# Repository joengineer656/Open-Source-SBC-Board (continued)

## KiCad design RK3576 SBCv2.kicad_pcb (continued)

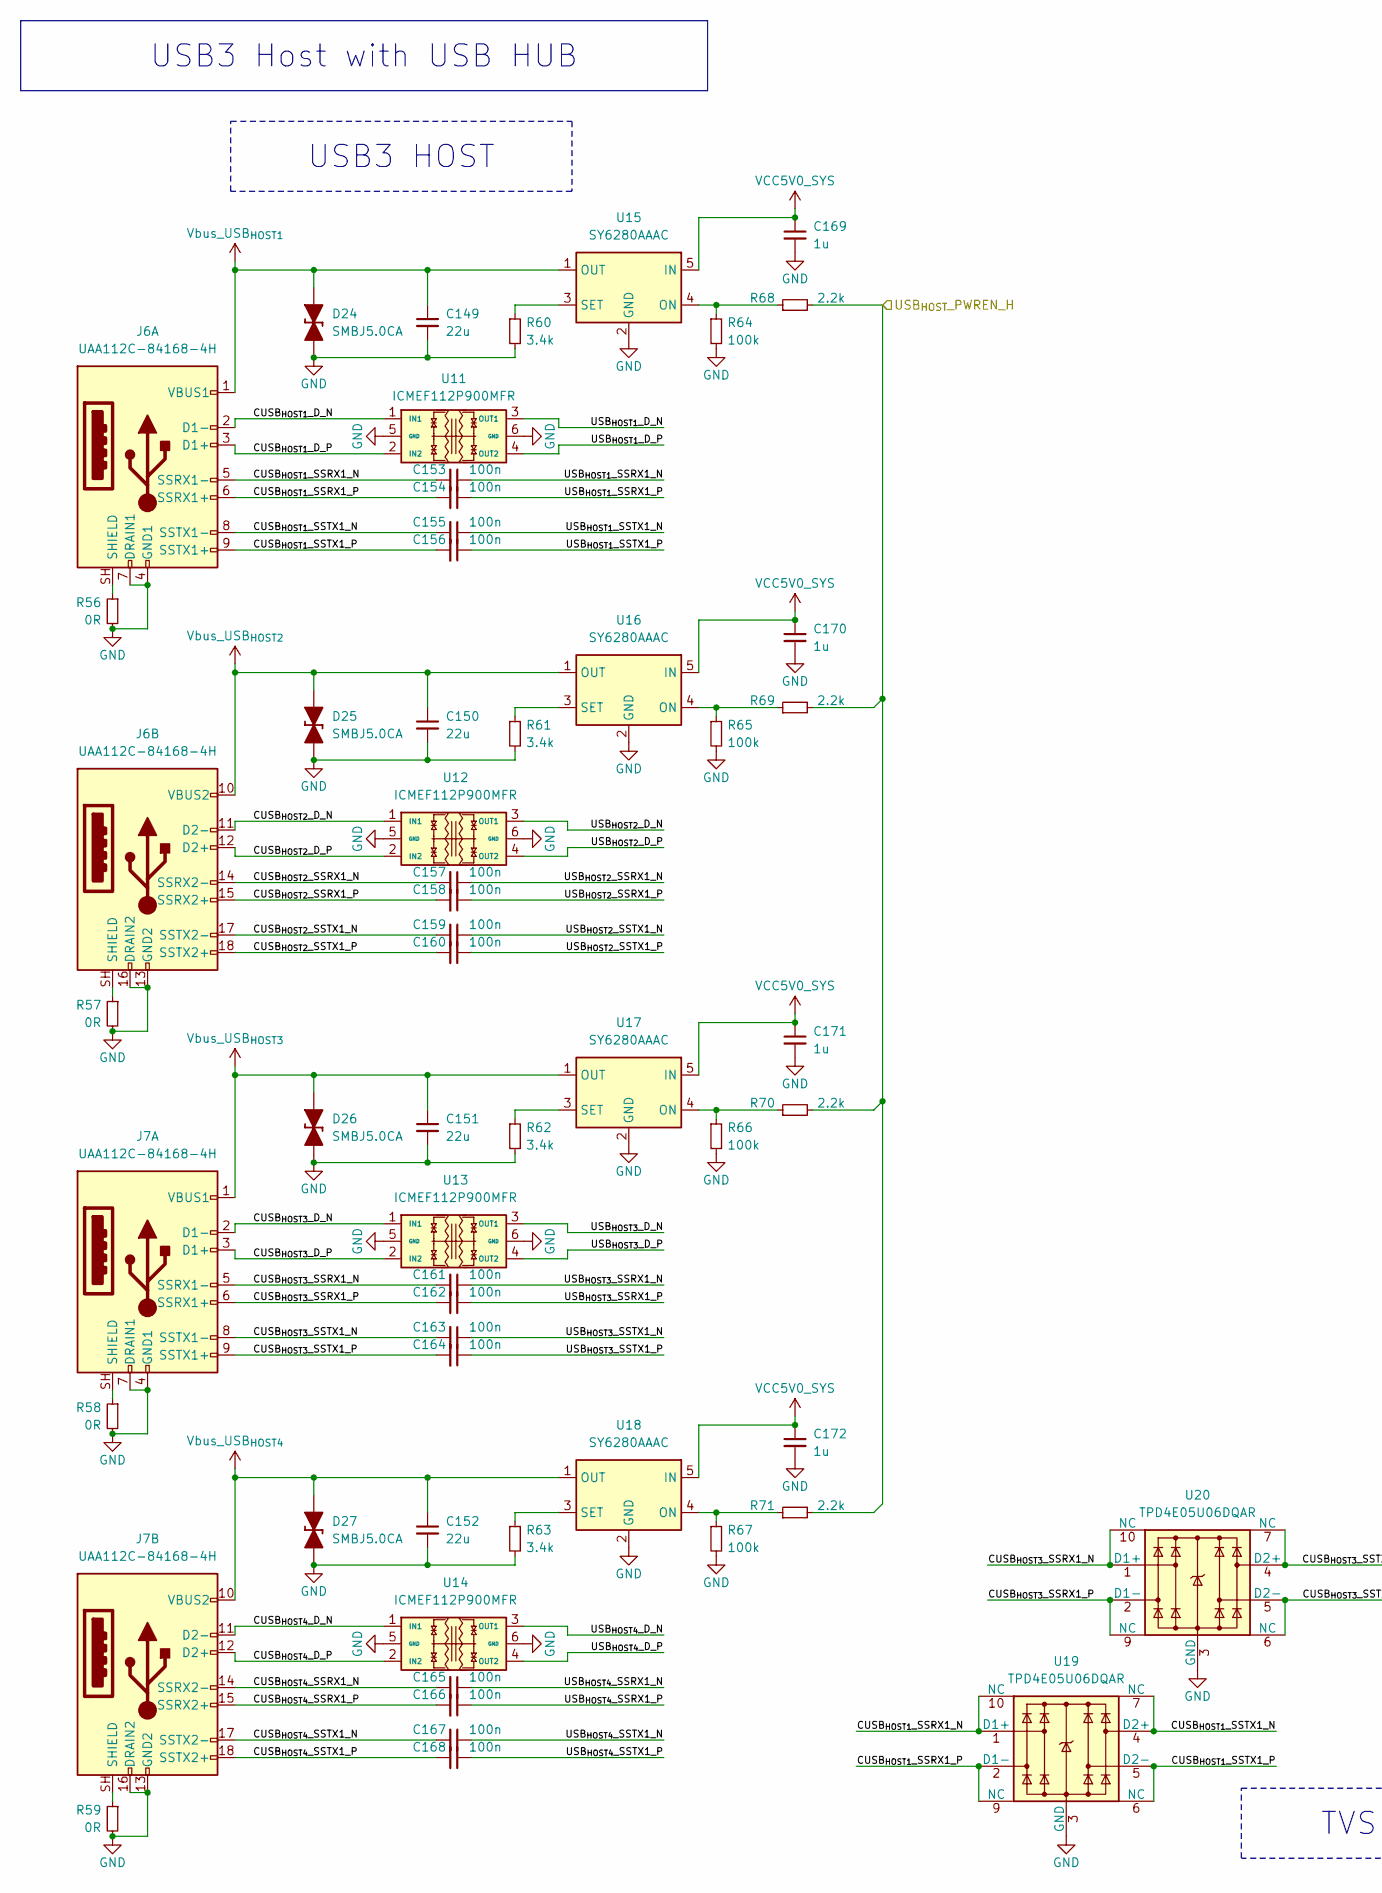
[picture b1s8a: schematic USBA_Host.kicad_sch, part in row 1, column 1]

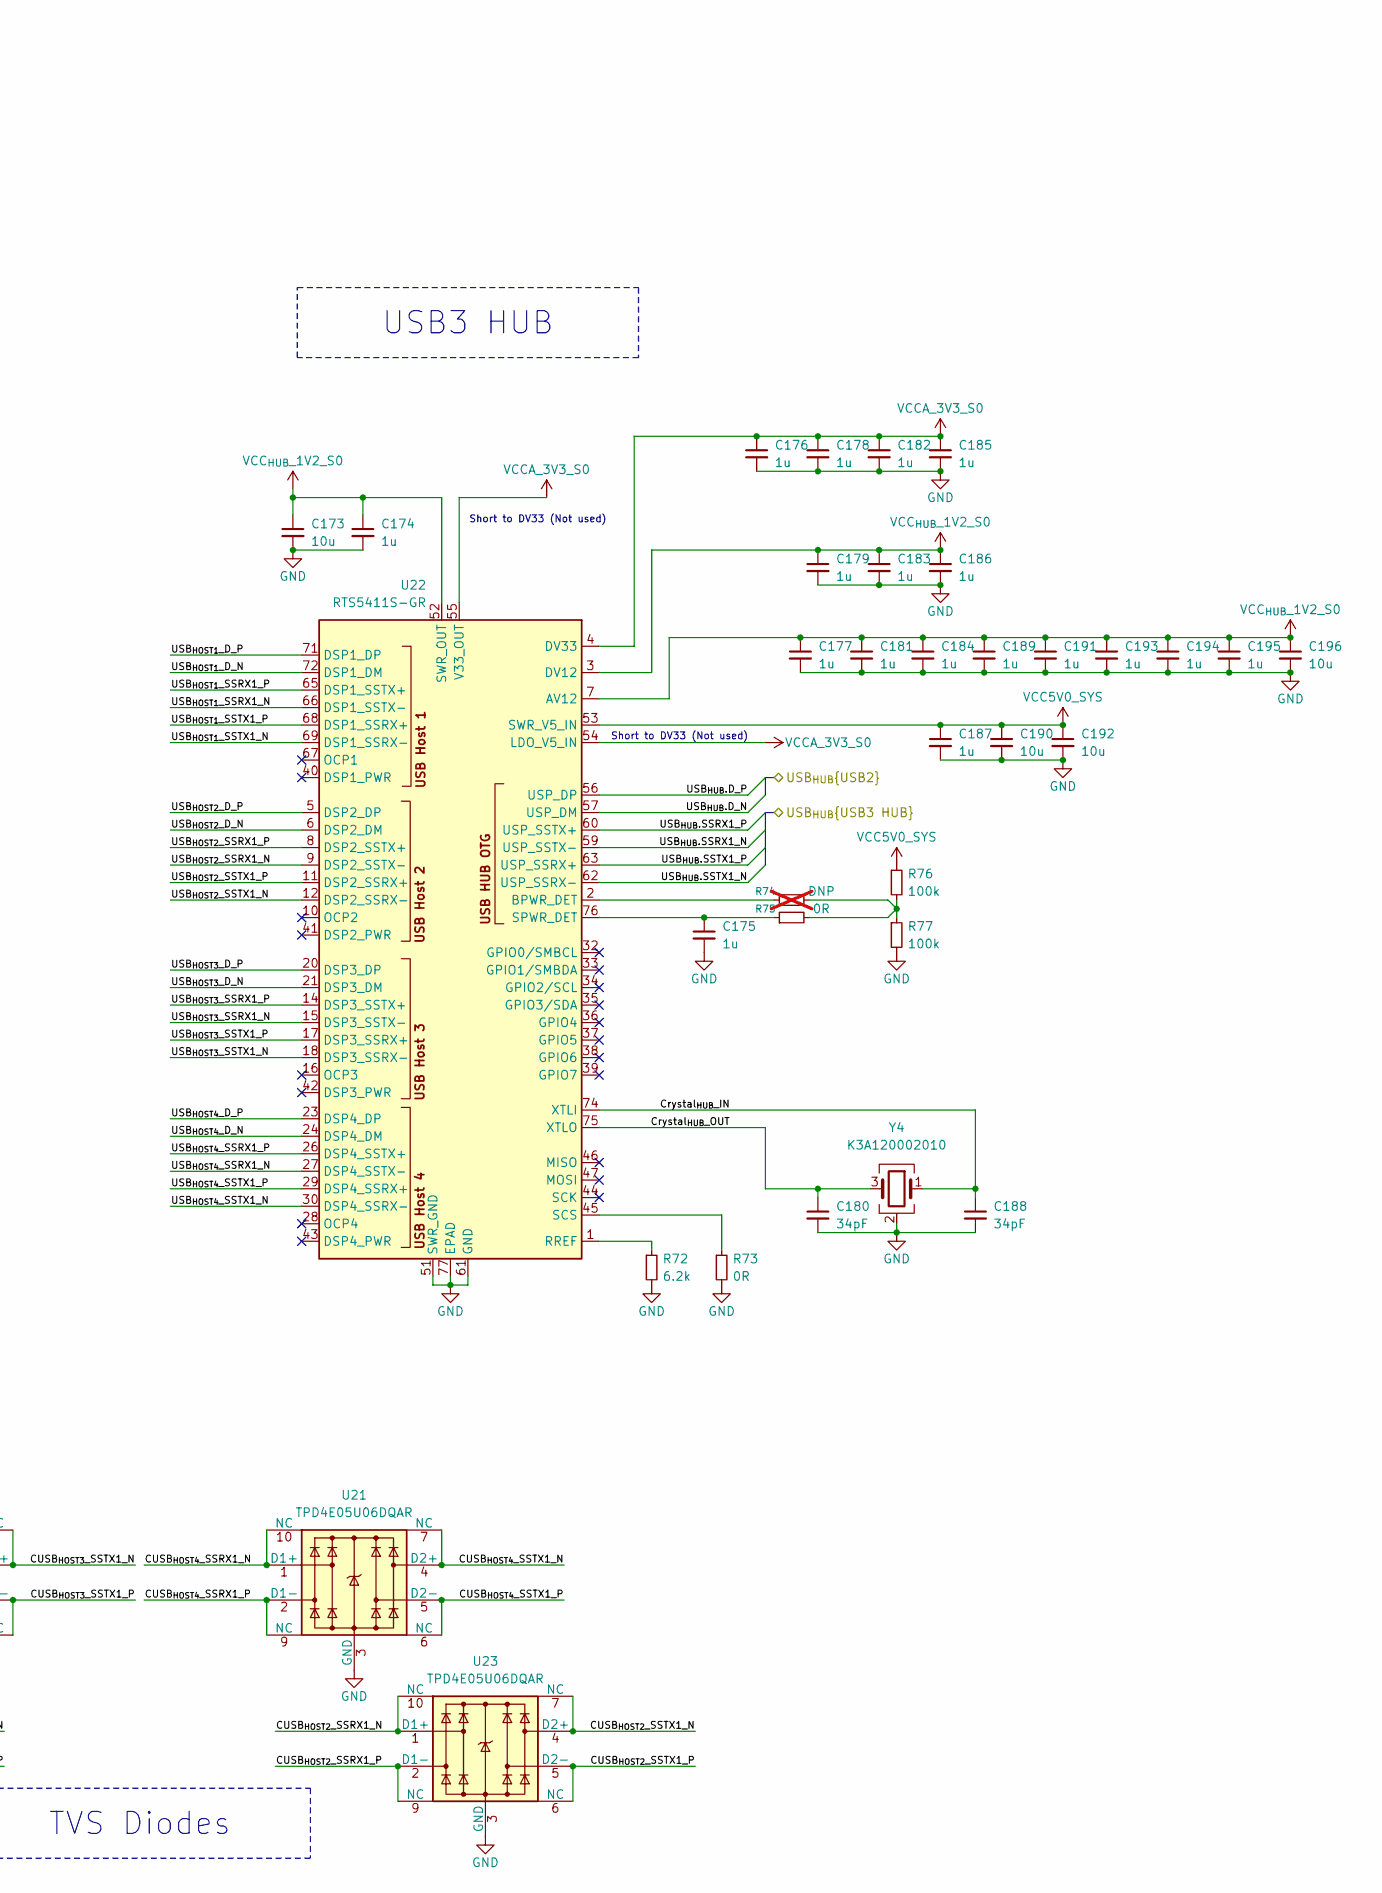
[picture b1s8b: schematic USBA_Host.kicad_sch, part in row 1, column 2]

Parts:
C149, C150, C151, C152: 22u; C_0603_1608Metric; Mouser Part CL10A226MP8NUNE; LCSC Part C86295
C153, C154, C155, C156, C157, C158, C159, C160: 100n; C_0201_0603Metric_Pad0.64x0.40mm_HandSolder; Mouser Part 187-CL03A104KO3NNNC; LCSC Part C307380
C161, C162, C163, C164, C165, C166, C167, C168: 100n; C_0201_0603Metric_Pad0.64x0.40mm_HandSolder; Mouser Part 187-CL03A104KO3NNND; LCSC Part C307380
C169, C170, C171, C172, C174, C175, C176, C177, C178, C179, C181, C182, C183, C184, C185, C186, C187, C189, C191, C193, C194, C195: 1u; C_0201_0603Metric_Pad0.64x0.40mm_HandSolder; Mouser Part CL03A105KP3NSNC; LCSC Part C5209398
C173, C190, C192, C196: 10u; C_0603_1608Metric; Mouser Part 187-CL10A106KP8NNNC; LCSC Part C19702
C180, C188: 34pF; C_0402_1005Metric; Mouser Part CC402JRNPO9BN360; LCSC Part C114394
D24, D25, D26, D27: SMBJ5.0CA; D_SMB_TVS; Mouser Part 581-SMBJ5.0CA; LCSC Part C113975
J6, J7: UAA112C-84168-4H; USB3_A_Molex_48406-0001_Horizontal_Stacked; LCSC Part C42403016
R56, R57, R58, R59, R73, R75: 0R; R_0402_1005Metric; Mouser Part 603-RC0402FR-070RL; LCSC Part C106231
R60, R61, R62, R63: 3.4k; R_0402_1005Metric; Mouser Part 603-RC0402FR-0715KL; LCSC Part C114761
R64, R65, R66, R67, R76, R77: 100k; R_0402_1005Metric; Mouser Part 603-RC0402FR-0710KL; LCSC Part C60490
R68, R69, R70, R71: 2.2k; R_0402_1005Metric; Mouser Part 603-RC0402FR-072K2L; LCSC Part C114762
R72: 6.2k; R_0402_1005Metric; Mouser Part 603-RT0402FRE076K2L; LCSC Part C854413
R74: DNP; R_0402_1005Metric; Mouser Part 603-RC0402FR-070RL; LCSC Part C106231; not fitted
U11, U12, U13, U14: ICMEF112P900MFR; LCSC Part C125058
U15, U16, U17, U18: SY6280AAAC; SOT-23-5; LCSC Part C207620
U19, U20, U21, U23: TPD4E05U06DQAR; USON-10_2.5x1.0mm_P0.5mm; Mouser Part 595-TPD4E05U06DQAR; LCSC Part C138714
U22: RTS5411S-GR; QFN-76-1EP_9x9mm_P0.4mm_EP5.81x6.31mm_ThermalVias; LCSC Part C5356838
Y4: K3A120002010; Crystal_SMD_3225-4Pin_3.2x2.5mm_HandSoldering; LCSC Part C368730

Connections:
/RK3576 SOC/USB_{HOST}_PWREN_H: R68.2, R69.2, R70.2, R71.2; also elsewhere on the board
/RK3576 SOC/USB_{HUB}.D_N: U22.57 (USP_DM); also elsewhere on the board
/RK3576 SOC/USB_{HUB}.D_P: U22.56 (USP_DP); also elsewhere on the board
/USB-A Host/CUSB_{HOST1}_D_N: J6.2 (D1-), U11.1 (IN1)
/USB-A Host/CUSB_{HOST1}_D_P: J6.3 (D1+), U11.2 (IN2)
/USB-A Host/CUSB_{HOST1}_SSRX1_N: C153.2, J6.5 (SSRX1-), U19.1 (D1+), U19.10 (NC)
/USB-A Host/CUSB_{HOST1}_SSRX1_P: C154.2, J6.6 (SSRX1+), U19.2 (D1-), U19.9 (NC)
/USB-A Host/CUSB_{HOST1}_SSTX1_N: C155.2, J6.8 (SSTX1-), U19.4 (D2+), U19.7 (NC)
/USB-A Host/CUSB_{HOST1}_SSTX1_P: C156.2, J6.9 (SSTX1+), U19.5 (D2-), U19.6 (NC)
/USB-A Host/CUSB_{HOST2}_D_N: J6.11 (D2-), U12.1 (IN1)
/USB-A Host/CUSB_{HOST2}_D_P: J6.12 (D2+), U12.2 (IN2)
/USB-A Host/CUSB_{HOST2}_SSRX1_N: C157.2, J6.14 (SSRX2-), U23.1 (D1+), U23.10 (NC)
/USB-A Host/CUSB_{HOST2}_SSRX1_P: C158.2, J6.15 (SSRX2+), U23.2 (D1-), U23.9 (NC)
/USB-A Host/CUSB_{HOST2}_SSTX1_N: C159.2, J6.17 (SSTX2-), U23.4 (D2+), U23.7 (NC)
/USB-A Host/CUSB_{HOST2}_SSTX1_P: C160.2, J6.18 (SSTX2+), U23.5 (D2-), U23.6 (NC)
/USB-A Host/CUSB_{HOST3}_D_N: J7.2 (D1-), U13.1 (IN1)
/USB-A Host/CUSB_{HOST3}_D_P: J7.3 (D1+), U13.2 (IN2)
/USB-A Host/CUSB_{HOST3}_SSRX1_N: C161.2, J7.5 (SSRX1-), U20.1 (D1+), U20.10 (NC)
/USB-A Host/CUSB_{HOST3}_SSRX1_P: C162.2, J7.6 (SSRX1+), U20.2 (D1-), U20.9 (NC)
/USB-A Host/CUSB_{HOST3}_SSTX1_N: C163.2, J7.8 (SSTX1-), U20.4 (D2+), U20.7 (NC)
/USB-A Host/CUSB_{HOST3}_SSTX1_P: C164.2, J7.9 (SSTX1+), U20.5 (D2-), U20.6 (NC)
/USB-A Host/CUSB_{HOST4}_D_N: J7.11 (D2-), U14.1 (IN1)
/USB-A Host/CUSB_{HOST4}_D_P: J7.12 (D2+), U14.2 (IN2)
/USB-A Host/CUSB_{HOST4}_SSRX1_N: C165.2, J7.14 (SSRX2-), U21.1 (D1+), U21.10 (NC)
/USB-A Host/CUSB_{HOST4}_SSRX1_P: C166.2, J7.15 (SSRX2+), U21.2 (D1-), U21.9 (NC)
/USB-A Host/CUSB_{HOST4}_SSTX1_N: C167.2, J7.17 (SSTX2-), U21.4 (D2+), U21.7 (NC)
/USB-A Host/CUSB_{HOST4}_SSTX1_P: C168.2, J7.18 (SSTX2+), U21.5 (D2-), U21.6 (NC)
/USB-A Host/Crystal_{HUB}_IN: C188.1, U22.74 (XTLI), Y4.1
/USB-A Host/Crystal_{HUB}_OUT: C180.1, U22.75 (XTLO), Y4.3
/USB-A Host/USB_{HOST1}_D_N: U11.3 (OUT1), U22.72 (DSP1_DM)
/USB-A Host/USB_{HOST1}_D_P: U11.4 (OUT2), U22.71 (DSP1_DP)
/USB-A Host/USB_{HOST1}_SSRX1_N: C153.1, U22.66 (DSP1_SSTX-)
/USB-A Host/USB_{HOST1}_SSRX1_P: C154.1, U22.65 (DSP1_SSTX+)
/USB-A Host/USB_{HOST1}_SSTX1_N: C155.1, U22.69 (DSP1_SSRX-)
/USB-A Host/USB_{HOST1}_SSTX1_P: C156.1, U22.68 (DSP1_SSRX+)
/USB-A Host/USB_{HOST2}_D_N: U12.3 (OUT1), U22.6 (DSP2_DM)
/USB-A Host/USB_{HOST2}_D_P: U12.4 (OUT2), U22.5 (DSP2_DP)
/USB-A Host/USB_{HOST2}_SSRX1_N: C157.1, U22.9 (DSP2_SSTX-)
/USB-A Host/USB_{HOST2}_SSRX1_P: C158.1, U22.8 (DSP2_SSTX+)
/USB-A Host/USB_{HOST2}_SSTX1_N: C159.1, U22.12 (DSP2_SSRX-)
/USB-A Host/USB_{HOST2}_SSTX1_P: C160.1, U22.11 (DSP2_SSRX+)
/USB-A Host/USB_{HOST3}_D_N: U13.3 (OUT1), U22.21 (DSP3_DM)
/USB-A Host/USB_{HOST3}_D_P: U13.4 (OUT2), U22.20 (DSP3_DP)
/USB-A Host/USB_{HOST3}_SSRX1_N: C161.1, U22.15 (DSP3_SSTX-)
/USB-A Host/USB_{HOST3}_SSRX1_P: C162.1, U22.14 (DSP3_SSTX+)
/USB-A Host/USB_{HOST3}_SSTX1_N: C163.1, U22.18 (DSP3_SSRX-)
/USB-A Host/USB_{HOST3}_SSTX1_P: C164.1, U22.17 (DSP3_SSRX+)
/USB-A Host/USB_{HOST4}_D_N: U14.3 (OUT1), U22.24 (DSP4_DM)
/USB-A Host/USB_{HOST4}_D_P: U14.4 (OUT2), U22.23 (DSP4_DP)
/USB-A Host/USB_{HOST4}_SSRX1_N: C165.1, U22.27 (DSP4_SSTX-)
/USB-A Host/USB_{HOST4}_SSRX1_P: C166.1, U22.26 (DSP4_SSTX+)
/USB-A Host/USB_{HOST4}_SSTX1_N: C167.1, U22.30 (DSP4_SSRX-)
/USB-A Host/USB_{HOST4}_SSTX1_P: C168.1, U22.29 (DSP4_SSRX+)
/USB-A Host/USB_{HUB}.SSRX1_N: U22.59 (USP_SSTX-)
/USB-A Host/USB_{HUB}.SSRX1_P: U22.60 (USP_SSTX+)
/USB-A Host/USB_{HUB}.SSTX1_N: U22.62 (USP_SSRX-)
/USB-A Host/USB_{HUB}.SSTX1_P: U22.63 (USP_SSRX+)
unnamed: R74.2, R75.2, R76.2, R77.1
unnamed: R64.1, R68.1, U15.4 (ON)
unnamed: R60.1, U15.3 (SET)
unnamed: R65.1, R69.1, U16.4 (ON)
unnamed: R61.1, U16.3 (SET)
unnamed: R66.1, R70.1, U17.4 (ON)
unnamed: R62.1, U17.3 (SET)
unnamed: R67.1, R71.1, U18.4 (ON)
unnamed: R63.1, U18.3 (SET)
unnamed: R74.1, U22.2 (BPWR_DET)
unnamed: R72.1, U22.1 (RREF)
unnamed: R73.1, U22.45 (SCS)
unnamed: C175.1, R75.1, U22.76 (SPWR_DET)
VCC_{HUB}_1V2_S0: C173.1, C174.1, C177.1, C179.1, C181.1, C183.1, C184.1, C186.1, C189.1, C191.1, C193.1, C194.1, C195.1, C196.1, U22.3 (DV12), U22.7 (AV12), U22.13 (AV12), U22.19 (AV12), U22.25 (AV12), U22.31 (AV12), U22.49 (DV12), U22.50 (DV12), U22.52 (SWR_OUT), U22.58 (AV12), U22.64 (AV12), U22.70 (AV12)
Vbus_USB_{HOST1}: C149.1, D24.2 (A), J6.1 (VBUS1), U15.1 (OUT)
Vbus_USB_{HOST2}: C150.1, D25.2 (A), J6.10 (VBUS2), U16.1 (OUT)
Vbus_USB_{HOST3}: C151.1, D26.2 (A), J7.1 (VBUS1), U17.1 (OUT)
Vbus_USB_{HOST4}: C152.1, D27.2 (A), J7.10 (VBUS2), U18.1 (OUT)

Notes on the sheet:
Short to DV33 (Not used)
USB3 HUB
USB3 Host with USB HUB
TVS Diodes
USB3 HOST

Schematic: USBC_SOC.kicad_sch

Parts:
C131, C132, C133, C134, C135, C136, C137, C138, C139, C140: 100n; C_0201_0603Metric_Pad0.64x0.40mm_HandSolder; Mouser Part 187-CL03A104KO3NNNC; LCSC Part C307380
C141: 22u; C_0603_1608Metric; Mouser Part CL10A226MP8NUNE; LCSC Part C86295
C142: DNP; C_0201_0603Metric_Pad0.64x0.40mm_HandSolder; not fitted
C143, C144: 200pF; C_0402_1005Metric; Mouser Part 603-CC402JRNPO9BN201; LCSC Part C325462
C145, C146, C147, C148: 1u; C_0201_0603Metric_Pad0.64x0.40mm_HandSolder; Mouser Part CL03A105KP3NSNC; LCSC Part C5209398
D21: SMBJ5.0CA; D_SMB_TVS; Mouser Part 581-SMBJ5.0CA; LCSC Part C113975
D22, D23: PESD5V0S1BA; D_SOD-323_TVS; Mouser Part 771-PESD5V0S1BA-T/R; LCSC Part C5158048
J5: USB_C_Receptacle; USB-C-SMD_GT-USB-7092B; LCSC Part C22471967
R47: 0R; R_0402_1005Metric; Mouser Part 603-RC0402FR-070RL; LCSC Part C106231
R48, R49: 2M; R_0402_1005Metric; Mouser Part 603-RC0402FR-0710KL; LCSC Part C60490
R50, R51: 100k; R_0402_1005Metric; Mouser Part 603-RC0402FR-0710KL; LCSC Part C60490
R52, R53, R54: 10k; R_0402_1005Metric; Mouser Part 603-RC0402FR-0710KL; LCSC Part C60490
R55: 22R; R_0402_1005Metric; Mouser Part 603-RC0402FR-070RL; LCSC Part C106231
U5: ICMEF112P900MFR; LCSC Part C125058
U6: TPS22953DQCR; WSON-10-2x3-EP_TPS22953DQCR; LCSC Part C471046
U7: FUSB302BMPX; WQFN-14-1EP_2.5x2.5mm_P0.5mm_EP1.45x1.45mm; Mouser Part 512-FUSB302BMPX; LCSC Part C132291
U8, U9, U10: TPD4E05U06DQAR; USON-10_2.5x1.0mm_P0.5mm; Mouser Part 595-TPD4E05U06DQAR

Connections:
/RK3576 SOC/I2C2_SCL_M0_USB_Wireless: U7.6 (SCL); also elsewhere on the board
/RK3576 SOC/I2C2_SDA_M0_USB_Wireless: U7.7 (SDA); also elsewhere on the board
/RK3576 SOC/USB_{SOC}.D_N: U5.3 (OUT1); also elsewhere on the board
/RK3576 SOC/USB_{SOC}.D_P: U5.4 (OUT2); also elsewhere on the board
/RK3576 SOC/USB_{SOC}.PUPDCTRL1: R50.2; also elsewhere on the board
/RK3576 SOC/USB_{SOC}.PUPDCTRL2: R51.2; also elsewhere on the board
/RK3576 SOC/USB_{SOC}_CON_INT: U7.5 (INT_N); also elsewhere on the board
/RK3576 SOC/USB_{SOC}_PWREN_H: R55.2; also elsewhere on the board
/RK3576 SOC/Vdet_USB_{SOC}: R52.2, R53.1; also elsewhere on the board
/USB-C SOC/CUSB_{SOC}_AUX_N: C140.2, J5.B8 (SBU2), R49.1, R51.1, U10.5 (D2-), U10.6 (NC)
/USB-C SOC/CUSB_{SOC}_AUX_P: C139.2, J5.A8 (SBU1), R48.1, R50.1, U10.4 (D2+), U10.7 (NC)
/USB-C SOC/CUSB_{SOC}_D_N: J5.A7 (D-), J5.B7 (D-), U5.1 (IN1), U8.1 (D1+), U8.10 (NC)
/USB-C SOC/CUSB_{SOC}_D_P: J5.A6 (D+), J5.B6 (D+), U5.2 (IN2), U8.2 (D1-), U8.9 (NC)
/USB-C SOC/CUSB_{SOC}_RX1_N: C131.2, J5.B10 (RX1-), U8.4 (D2+), U8.7 (NC)
/USB-C SOC/CUSB_{SOC}_RX1_P: C132.2, J5.B11 (RX1+), U8.5 (D2-), U8.6 (NC)
/USB-C SOC/CUSB_{SOC}_RX2_N: C135.2, J5.A10 (RX2-), U9.4 (D2+), U9.7 (NC)
/USB-C SOC/CUSB_{SOC}_RX2_P: C136.2, J5.A11 (RX2+), U9.5 (D2-), U9.6 (NC)
/USB-C SOC/CUSB_{SOC}_TX1_N: C133.2, J5.A3 (TX1-), U9.1 (D1+), U9.10 (NC)
/USB-C SOC/CUSB_{SOC}_TX1_P: C134.2, J5.A2 (TX1+), U9.2 (D1-), U9.9 (NC)
/USB-C SOC/CUSB_{SOC}_TX2_N: C137.2, J5.B3 (TX2-), U10.1 (D1+), U10.10 (NC)
/USB-C SOC/CUSB_{SOC}_TX2_P: C138.2, J5.B2 (TX2+), U10.2 (D1-), U10.9 (NC)
/USB-C SOC/USB_{SOC}.AUX_N: C140.1
/USB-C SOC/USB_{SOC}.AUX_P: C139.1
/USB-C SOC/USB_{SOC}.RX1_N: C131.1
/USB-C SOC/USB_{SOC}.RX1_P: C132.1
/USB-C SOC/USB_{SOC}.RX2_N: C135.1
/USB-C SOC/USB_{SOC}.RX2_P: C136.1
/USB-C SOC/USB_{SOC}.TX1_N: C133.1
/USB-C SOC/USB_{SOC}.TX1_P: C134.1
/USB-C SOC/USB_{SOC}.TX2_N: C137.1
/USB-C SOC/USB_{SOC}.TX2_P: C138.1
/USB-C SOC/USB_{SOC}_CC1: C143.1, D22.2 (A), J5.A5 (CC1), U7.10 (CC1), U7.11 (CC1)
/USB-C SOC/USB_{SOC}_CC2: C144.1, D23.2 (A), J5.B5 (CC2), U7.1 (CC2), U7.14 (CC2)
unnamed: J5.SH (SHIELD), R47.1
unnamed: C142.1, U6.6 (CT)
unnamed: R54.1, R55.1, U6.4 (EN)
Vbus_USB_{OTG}: C141.1, D21.2 (A), J5.A4 (VBUS), J5.A9 (VBUS), J5.B4 (VBUS), J5.B9 (VBUS), R52.1, U6.8 (SNS), U6.9 (OUT), U6.10 (OUT), U7.2 (VBUS)

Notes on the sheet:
Need rating 25v or higher
USB3.2 OTG With Controller
TVS Diodes
USB_{SOC} Power EN

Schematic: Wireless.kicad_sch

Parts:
C248, C249, C250: 1u; C_0201_0603Metric_Pad0.64x0.40mm_HandSolder; Mouser Part CL03A105KP3NSNC; LCSC Part C5209398
C251: 22u; C_0603_1608Metric; Mouser Part CL10A226MP8NUNE; LCSC Part C86295
J15: APCI0108-P001A; MPN APCI0108-P001A; LCSC Part C7498141
R177, R178, R179, R180, R181, R182: 22R; R_0402_1005Metric; Mouser Part 603-RC0402FR-070RL; LCSC Part C106231
R183: 10k; R_0402_1005Metric; Mouser Part 603-RC0402FR-0710KL; LCSC Part C60490; not fitted
R184, R185: 2.2k; R_0402_1005Metric; Mouser Part 603-RC0402FR-072K2L; LCSC Part C114762

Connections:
/RK3576 SOC/BT_REG_ON_L: J15.54 (~BT_REG_ON); also elsewhere on the board
/RK3576 SOC/BT_WAKE_DEV_L: J15.42 (~BT_DEV_WAKE_L); also elsewhere on the board
/RK3576 SOC/BT_WAKE_HOST_L: J15.20 (~BT_HOST_WAKE_L); also elsewhere on the board
/RK3576 SOC/I2C2_SCL_M0_USB_Wireless: J15.60 (I2C_SCL), R185.2; also elsewhere on the board
/RK3576 SOC/I2C2_SDA_M0_USB_Wireless: J15.58 (I2C_SDA), R184.2; also elsewhere on the board
/RK3576 SOC/SDMMC1.CLK_M0: R181.1; also elsewhere on the board
/RK3576 SOC/SDMMC1.CMD_M0: R182.1; also elsewhere on the board
/RK3576 SOC/WIFI_REG_ON_L: J15.56 (~WLAN_REG_ON); also elsewhere on the board
/RK3576 SOC/WIFI_WAKE_DEV_L: J15.40 (~WLAN_DEV_WAKE_L); also elsewhere on the board
/RK3576 SOC/WIFI_WAKE_HOST_L: J15.21 (~WLAN_HOST_WAKE_L); also elsewhere on the board
/RK3576 SOC/WIFI_nRST: J15.23 (~WLAN_RESET_N); also elsewhere on the board
/RK3576 SOC/WIRELESS_ALERT_L: J15.62 (~ALERT_N), R183.2; also elsewhere on the board
/RTC/RTC_32KOUT_WIFI: J15.50 (SUSCLK_32K); also elsewhere on the board
/Wireless/SAI2.LRCK_M0: J15.10 (BT_PCM_SYNC)
/Wireless/SAI2.SCLK_M0: J15.8 (BT_PCM_CLK)
/Wireless/SAI2.SDI_M0: J15.12 (BT_PCM_OUT)
/Wireless/SAI2.SDO_M0: J15.14 (BT_PCM_IN)
/Wireless/SDMMC1.CLK: J15.9 (WLAN_SDIO_CLK), R181.2
/Wireless/SDMMC1.CMD: J15.11 (WLAN_SDIO_CMD), R182.2
/Wireless/SDMMC1.D0: J15.13 (WLAN_SDIO_D0), R177.2
/Wireless/SDMMC1.D0_M0: R177.1
/Wireless/SDMMC1.D1: J15.15 (WLAN_SDIO_D1), R178.2
/Wireless/SDMMC1.D1_M0: R178.1
/Wireless/SDMMC1.D2: J15.17 (WLAN_SDIO_D2), R179.2
/Wireless/SDMMC1.D2_M0: R179.1
/Wireless/SDMMC1.D3: J15.19 (WLAN_SDIO_D3), R180.2
/Wireless/SDMMC1.D3_M0: R180.1
/Wireless/UART4.CTSN_M1: J15.34 (BT_UART_RTS)
/Wireless/UART4.RTSN_M1: J15.36 (BT_UART_CTS)
/Wireless/UART4.RX_M1: J15.22 (BT_UART_TXD)
/Wireless/UART4.TX_M1: J15.32 (BT_UART_RXD)

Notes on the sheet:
OUR Connect Support SDIO for WIFI and UART&PCM for Blutooth So Modules use PCIe and USB are not support
Wireless Module & Antennas
ALERT pin i used for wake up the Host SUSCLK is 32.768k Hz CLK IN the M.2 for the modules don't have it internal This pins Not used in alot of modules thats why we don't need it.

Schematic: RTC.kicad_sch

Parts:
BT1: BS-06-B4AA012; BAT-SMD_BS-06-B4AA012; LCSC Part C964758
C340, C341, C342: 1u; C_0201_0603Metric_Pad0.64x0.40mm_HandSolder; Mouser Part CL03A105KP3NSNC; LCSC Part C5209398
D59: SMBJ5.0CA; D_SMB_TVS; Mouser Part 581-SMBJ5.0CA; LCSC Part C113975
F1: 1812L010/100GR; Fuse_1812_4532Metric; LCSC Part C28326708
Q6: AO3401A; SOT-23; LCSC Part C347476
R200, R201: 2.2k; R_0402_1005Metric; Mouser Part 603-RC0402FR-072K2L; LCSC Part C114762
R202, R203: 10k; R_0402_1005Metric; Mouser Part 603-RC0402FR-0710KL; LCSC Part C60490
R204, R205: 22R; R_0402_1005Metric; Mouser Part 603-RC0402FR-070RL; LCSC Part C106231
U39: M24C64-RMN6TP; SOIC-8_3.9x4.9mm_P1.27mm; Mouser Part 511-M24C64-RMN6TP; LCSC Part C79988
U40: RV-3028-C7; MicroCrystal_C7_SON-8_1.5x3.2mm_P0.9mm; Mouser Part 428-203591-MG01

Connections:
/40pin GPIO/I2C8_SCL_M3_RTC_EEPROM: R200.2, U39.6 (SCL), U40.3 (SCL); also elsewhere on the board
/40pin GPIO/I2C8_SDA_M3_RTC_EEPROM: R201.2, U39.5 (SDA), U40.4 (SDA); also elsewhere on the board
/RK3576 SOC/EEPROM_WP: U39.7 (WP); also elsewhere on the board
/RK3576 SOC/RTC_32KOUT_SOC: R204.2; also elsewhere on the board
/RK3576 SOC/RTC_INT_L: U40.2 (~INT); also elsewhere on the board
/RTC/RTC_32KOUT_WIFI: R205.2; also elsewhere on the board
unnamed: BT1.1 (+), F1.2
unnamed: D59.2 (A), F1.1, Q6.3 (D)
unnamed: Q6.1 (G), R203.1
unnamed: C342.1, Q6.2 (S), U40.6 (VBACKUP)
unnamed: R202.2, R204.1, R205.1, U40.1 (CLKOUT)
VCC_3.3v_S0: C340.1, U39.8 (VDD); also elsewhere on the board

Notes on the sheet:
RTC & Backup BATT
EEPROM
RTC

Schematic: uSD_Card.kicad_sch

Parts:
C241, C243: 1u; C_0201_0603Metric_Pad0.64x0.40mm_HandSolder; Mouser Part CL03A105KP3NSNC; LCSC Part C5209398
C242: 22u; C_0603_1608Metric; Mouser Part CL10A226MP8NUNE; LCSC Part C86295
D30: SMBJ5.0CA; D_SMB_TVS; Mouser Part 581-SMBJ5.0CA; LCSC Part C113975
J13: TF PUSH; TF-PUSH_C393941; LCSC Part C393941
R153, R154, R155, R156, R157, R158: 4.7k; R_0402_1005Metric; Mouser Part 603-RC0402FR-074K7L; LCSC Part C105871; not fitted
R159: 4.7k; R_0402_1005Metric; Mouser Part 603-RC0402FR-074K7L; LCSC Part C105871
R160, R161, R162, R163, R164, R165, R166: 22R; R_0402_1005Metric; Mouser Part 603-RC0402FR-070RL; LCSC Part C106231
R167: 10k; R_0402_1005Metric; Mouser Part 603-RC0402FR-0710KL; LCSC Part C60490
R168: 100k; R_0402_1005Metric; Mouser Part 603-RC0402FR-0710KL; LCSC Part C60490
R169: 2.2k; R_0402_1005Metric; Mouser Part 603-RC0402FR-072K2L; LCSC Part C114762
U31, U32: TPD4E05U06DQAR; USON-10_2.5x1.0mm_P0.5mm; Mouser Part 595-TPD4E05U06DQAR; LCSC Part C138714
U33: AP2553W6-7; SOT-23-6_Handsoldering; Mouser Part 621-AP2553W6-7; LCSC Part C212302

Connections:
/RK3576 SOC/uSD_DET: R159.2, R166.1; also elsewhere on the board
/RK3576 SOC/uSD_PWREN_H: R169.2; also elsewhere on the board
/uSD Card/J_uSD_CLK: J13.5 (CLK), R163.2, U31.5 (D2-), U31.6 (NC)
/uSD Card/J_uSD_CMD: J13.3 (CMD), R162.2, U31.4 (D2+), U31.7 (NC)
/uSD Card/J_uSD_D0: J13.7 (DAT0), R164.2, U32.1 (D1+), U32.10 (NC)
/uSD Card/J_uSD_D1: J13.8 (DAT1), R165.2, U32.2 (D1-), U32.9 (NC)
/uSD Card/J_uSD_D2: J13.1 (DAT2), R160.2, U31.1 (D1+), U31.10 (NC)
/uSD Card/J_uSD_D3: J13.2 (DAT3/CD), R161.2, U31.2 (D1-), U31.9 (NC)
/uSD Card/J_uSD_DET: J13.9 (DET), R166.2, U32.4 (D2+), U32.7 (NC)
/uSD Card/uSD.CLK: R156.2, R163.1
/uSD Card/uSD.CMD: R155.2, R162.1
/uSD Card/uSD.D0: R157.2, R164.1
/uSD Card/uSD.D1: R158.2, R165.1
/uSD Card/uSD.D2: R153.2, R160.1
/uSD Card/uSD.D3: R154.2, R161.1
unnamed: R168.1, R169.1, U33.3 (EN)
unnamed: R167.1, U33.5 (ILIM)
VCC3V3_uSD: C241.1, C242.1, D30.2 (A), J13.4 (VDD), U33.6 (OUT)

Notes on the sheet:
uSD Card
When u use uSD Card in SDMMC Mode (what we done) u can boot from it
TVS Diodes

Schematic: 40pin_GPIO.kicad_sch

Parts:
C264, C265: 22u; C_0603_1608Metric; Mouser Part CL10A226MP8NUNE; LCSC Part C86295
C266, C267: 1u; C_0201_0603Metric_Pad0.64x0.40mm_HandSolder; Mouser Part CL03A105KP3NSNC; LCSC Part C5209398
D31, D32, D33, D34, D35, D36, D37, D38, D39, D40, D41, D42, D43, D44, D45, D46, D47, D48, D49, D50, D51, D52, D54, D56: PESD5V0S1BA; D_SOD-323_TVS; Mouser Part 771-PESD5V0S1BA-T/R; LCSC Part C5158048
D53, D55, D57, D58: SMBJ5.0CA; D_SMB_TVS; Mouser Part 581-SMBJ5.0CA; LCSC Part C113975
J18: B-2100S40P-B110; PinSocket_2x20_P2.54mm_Horizontal; LCSC Part C124383
J19: B3B-XH-A(LF)(SN); FanPinHeader_1x03_P2.54mm_Vertical; LCSC Part C144394
R188, R190, R191: 10k; R_0402_1005Metric; Mouser Part 603-RC0402FR-0710KL; LCSC Part C60490
R189: 10K; R_0402_1005Metric; Mouser Part 603-RC0402FR-0710KL; LCSC Part C60490
R192, R193: 100k; R_0402_1005Metric; Mouser Part 603-RC0402FR-0710KL; LCSC Part C60490
R194, R195: 2.2k; R_0402_1005Metric; Mouser Part 603-RC0402FR-072K2L; LCSC Part C114762
R196: 22R; R_0402_1005Metric; Mouser Part 603-RC0402FR-070RL; LCSC Part C106231
U35, U36: AP2553W6-7; SOT-23-6_Handsoldering; Mouser Part 621-AP2553W6-7; LCSC Part C212302

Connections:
/40pin GPIO/40GPIOs.GPIO(3_A6)_UART(1)_RX-M2: D43.2 (A), J18.27 (ID_SD_I2C0/GPIO00)
/40pin GPIO/40GPIOs.GPIO(3_A7)_UART(1)_TX-M2: D45.2 (A), J18.28 (ID_SC_I2C0/GPIO01)
/40pin GPIO/40GPIOs.GPIO(3_B0)_UART(10)_RX-M0: D38.2 (A), J18.8 (GPIO14/UART_TXD)
/40pin GPIO/40GPIOs.GPIO(3_B1)_UART(10)_TX-M0: D36.2 (A), J18.10 (GPIO15/UART_RXD)
/40pin GPIO/40GPIOs.GPIO(3_B4)_PWM(1)_CH4-M3: D39.2 (A), J18.16 (GPIO23/SDIO_CMD)
/40pin GPIO/40GPIOs.GPIO(3_B5)_PWM(1)_CH5-M3: D40.2 (A), J18.33 (GPIO13/PWM1)
/40pin GPIO/40GPIOs.GPIO(3_B6)_PWM(0)_CH1-M3: D42.2 (A), J18.32 (GPIO12/PWM0)
/40pin GPIO/40GPIOs.GPIO(3_B7)_UART(2)_RX-M2: D37.2 (A), J18.18 (GPIO24/SDIO_DAT0)
/40pin GPIO/40GPIOs.GPIO(3_C0)_UART(2)_TX-M2: D35.2 (A), J18.22 (GPIO25/SDIO_DAT1)
/40pin GPIO/40GPIOs.GPIO(3_C1)_I2C(5)_SDA-M3: D33.2 (A), J18.37 (GPIO26/SDIO_DAT2)
/40pin GPIO/40GPIOs.GPIO(3_C2)_I2C(9)_SCL-M3: D54.2 (A), J18.19 (MOSI_SPI0/GPIO10)
/40pin GPIO/40GPIOs.GPIO(3_C3)_I2C(9)_SDA-M3: D51.2 (A), J18.21 (MISO_SPI0/GPIO09)
/40pin GPIO/40GPIOs.GPIO(3_C4)_I2C(5)_SCL-M3: D31.2 (A), J18.13 (GPIO27/SDIO_DAT3)
/40pin GPIO/40GPIOs.GPIO(3_C5)_PWM(2)_CH2-M3: D41.2 (A), J18.15 (GPIO22/SDIO_CLK)
/40pin GPIO/40GPIOs.GPIO(3_C6): D34.2 (A), J18.36 (GPIO16/SPI1_~CE2)
/40pin GPIO/40GPIOs.GPIO(3_C7): D32.2 (A), J18.11 (GPIO17/SPI1_~CE1)
/40pin GPIO/I2C2_SCL_M0_CC_RTC_EEPROM: D49.2 (A), J18.5 (SCL_I2C1/GPIO03)
/40pin GPIO/I2C2_SDA_M0_CC_RTC_EEPROM: D47.2 (A), J18.3 (SDA_I2C1/GPIO02)
/40pin GPIO/SPI1_{MCU}.CS: D48.2 (A), J18.12 (GPIO18/SPI1_~CE0/PCM_CLK/PWM0); also elsewhere on the board
/40pin GPIO/SPI1_{MCU}.SCK: D56.2 (A), J18.40 (GPIO21/SPI1_SCLK/PCM_DOUT); also elsewhere on the board
/40pin GPIO/SPI1_{MCU}.SDI: D52.2 (A), J18.38 (GPIO20/SPI1_MOSI/PCM_DIN/PWM1); also elsewhere on the board
/40pin GPIO/SPI1_{MCU}.SDO: D50.2 (A), J18.35 (GPIO19/SPI1_MISO/PCM_FS); also elsewhere on the board
/RK3576 SOC/SARADC_VIN4_IN: R188.1, R189.1; also elsewhere on the board
unnamed: J18.23 (SCLK_SPI0/GPIO11), R188.2
unnamed: R190.1, U35.5 (ILIM)
unnamed: R191.1, U36.5 (ILIM)
VCC_{GPIO}_3V3_S0: C264.1, D46.2 (A), D53.2 (A), J18.1 (3V3), J18.17 (3V3), U35.6 (OUT); also elsewhere on the board
VCC_{GPIO}_5V0_S0: C265.1, D44.2 (A), D55.2 (A), J18.2 (5V), J18.4 (5V), U36.6 (OUT); also elsewhere on the board

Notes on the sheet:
The Power in GPIO Pin Header is OUTPUT ONLY
40PIN GPIO Connector

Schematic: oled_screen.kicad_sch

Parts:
C343: 10u; C_0603_1608Metric; Mouser Part 187-CL10A106KP8NNNC; LCSC Part C19702
C344, C345: 1u; C_0201_0603Metric_Pad0.64x0.40mm_HandSolder; Mouser Part CL03A105KP3NSNC; LCSC Part C5209398
R206: 240R; R_0402_1005Metric; Mouser Part 603-RC0402FR-07240RL; LCSC Part C114755
R207: 10k; R_0402_1005Metric; Mouser Part 603-RC0402FR-0710KL; LCSC Part C60490
U41: 0.96 OLED Display 8 pins; FFC-SMD_8P-P0.50_AFC42-S08FMA-1H_BOTTOM; MPN HS154L01W4S01; LCSC Part C18723032

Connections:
/OLED Screen/OLED.CLK: U41.6 (SCL); also elsewhere on the board
/OLED Screen/OLED.CS: U41.8 (CS); also elsewhere on the board
/OLED Screen/OLED.LED: C345.1, R206.2, U41.1 (LEDA); also elsewhere on the board
/OLED Screen/OLED.MOSI: U41.5 (SDA); also elsewhere on the board
/OLED Screen/OLED.RS: U41.4 (RS); also elsewhere on the board
/OLED Screen/OLED.nRST: R207.2, U41.3 (RESET); also elsewhere on the board

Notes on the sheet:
OLED Screen

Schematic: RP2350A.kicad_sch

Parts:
C113: 22u; C_0603_1608Metric; Mouser Part CL10A226MP8NUNE; LCSC Part C86295
C114, C115, C116, C117, C120, C121, C122, C123, C124, C125, C126, C127, C128, C129, C130: 1u; C_0201_0603Metric_Pad0.64x0.40mm_HandSolder; Mouser Part CL03A105KP3NSNC; LCSC Part C5209398
C118, C119: 34pF; C_0402_1005Metric; Mouser Part CC402JRNPO9BN360; LCSC Part C114394
D4: SMBJ5.0CA; D_SMB_TVS; Mouser Part 581-SMBJ5.0CA; LCSC Part C113975
D5, D6, D7, D8, D9, D10, D11, D12, D13, D14, D15, D16, D17, D18, D19, D20: PESD5V0S1BA; D_SOD-323_TVS; Mouser Part 771-PESD5V0S1BA-T/R; LCSC Part C5158048
J2: TYPEC-305-ACP16H458; USB-C-SMD_TYPEC-305-ACP16H458; LCSC Part C5454943
J3: JTag Connector; Tag-Connect_TC2030-IDC-NL_2x03_P1.27mm_Vertical
J4: B-2100S20P-B110; PinSocket_2x10_P2.54mm_Horizontal; LCSC Part C124359
L1: 3.3uH; L_Coilcraft_0805HQ_2012Metric; LCSC Part C2926398
R36, R43: 0R; R_0402_1005Metric; Mouser Part 603-RC0402FR-070RL; LCSC Part C106231
R37, R38, R46: 5.1k; R_0402_1005Metric; Mouser Part 603-RC0402FR-075K1L; LCSC Part C105872
R39: 100k; R_0402_1005Metric; Mouser Part 603-RC0402FR-0710KL; LCSC Part C60490
R40, R45: 10k; R_0402_1005Metric; Mouser Part 603-RC0402FR-0710KL; LCSC Part C60490
R41: 4.7k; R_0402_1005Metric; Mouser Part 603-RC0402FR-074K7L; LCSC Part C105871
R42, R44: 1k; R_0402_1005Metric; Mouser Part 603-RC0402FR-071KL; LCSC Part C106235
SW3, SW4: XUNPU TS-1089S-02526; LCSC Part C455282
U2: ETA7014S2G; TSOT-23-6; LCSC Part C7465500
U3: W25Q128JVS; SOIC-8_5.3x5.3mm_P1.27mm; Mouser Part 454-W25Q128JVSIQTR; LCSC Part C97521
U4: RP2350A; QFN-60-1EP_7x7mm_P0.4mm_EP3.4x3.4mm; Mouser Part 358-SC150913; LCSC Part C42411118
Y3: TAXM12M4RLBDDT2T; Crystal_SMD_3225-4Pin_3.2x2.5mm_HandSoldering; LCSC Part C133334

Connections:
/40pin GPIO/SPI1_{MCU}.CS: U4.17 (GPIO13); also elsewhere on the board
/40pin GPIO/SPI1_{MCU}.SCK: U4.18 (GPIO14); also elsewhere on the board
/40pin GPIO/SPI1_{MCU}.SDI: U4.16 (GPIO12); also elsewhere on the board
/40pin GPIO/SPI1_{MCU}.SDO: U4.19 (GPIO15); also elsewhere on the board
/OLED Screen/OLED.CLK: U4.29 (GPIO18); also elsewhere on the board
/OLED Screen/OLED.CS: U4.28 (GPIO17); also elsewhere on the board
/OLED Screen/OLED.LED: U4.27 (GPIO16); also elsewhere on the board
/OLED Screen/OLED.MOSI: U4.31 (GPIO19); also elsewhere on the board
/OLED Screen/OLED.RS: U4.33 (GPIO21); also elsewhere on the board
/OLED Screen/OLED.nRST: U4.32 (GPIO20); also elsewhere on the board
/RK3576 SOC/Vdet_USB_{MCU}: R40.2, R41.1; also elsewhere on the board
/RP2350A MCU/ADC0_{MCU}: D12.2 (A), J4.15, U4.40 (GPIO26/ADC0)
/RP2350A MCU/ADC1_{MCU}: D10.2 (A), J4.16, U4.41 (GPIO27/ADC1)
/RP2350A MCU/ADC2_{MCU}: D8.2 (A), J4.17, U4.42 (GPIO28/ADC2)
/RP2350A MCU/ADC3_{MCU}: D7.2 (A), J4.18, U4.43 (GPIO29/ADC3)
/RP2350A MCU/Crystal_{MCU}_IN: C118.1, U4.21 (XIN), Y3.1
/RP2350A MCU/Crystal_{MCU}_OUT: C119.1, U4.22 (XOUT), Y3.3
/RP2350A MCU/Flash_{MCU}_CLK: U3.6 (CLK), U4.56 (QSPI_SCLK)
/RP2350A MCU/Flash_{MCU}_SD0: U3.5 (DI/IO_{0}), U4.57 (QSPI_SD0)
/RP2350A MCU/Flash_{MCU}_SD1: U3.2 (DO/IO_{1}), U4.59 (QSPI_SD1)
/RP2350A MCU/Flash_{MCU}_SD2: U3.3 (~WP/IO_{2}), U4.58 (QSPI_SD2)
/RP2350A MCU/Flash_{MCU}_SD3: U3.7 (~HOLD/~RESET/IO_{3}), U4.55 (QSPI_SD3)
/RP2350A MCU/Flash_{MCU}_SS: R43.2, U4.60 (~QSPI_SS)
/RP2350A MCU/GPIO_{MCU}_6: D15.2 (A), J4.7, U4.9 (GPIO6)
/RP2350A MCU/GPIO_{MCU}_7: D16.2 (A), J4.8, U4.10 (GPIO7)
/RP2350A MCU/GPIO_{MCU}_22: D19.2 (A), J4.11, U4.34 (GPIO22)
/RP2350A MCU/GPIO_{MCU}_23: D20.2 (A), J4.12, U4.35 (GPIO23)
/RP2350A MCU/GPIO_{MCU}_24: D6.2 (A), J4.13, U4.36 (GPIO24)
/RP2350A MCU/GPIO_{MCU}_25: D5.2 (A), J4.14, U4.37 (GPIO25)
/RP2350A MCU/I2C0_{MCU}_SCL: D14.2 (A), J4.6, U4.8 (GPIO5)
/RP2350A MCU/I2C0_{MCU}_SDA: D13.2 (A), J4.5, U4.7 (GPIO4)
/RP2350A MCU/Reset_{MCU}: J3.3 (~RESET), R44.2, R45.2, U4.26 (RUN)
/RP2350A MCU/SWCLK_{MCU}: J3.4 (SWCLK), U4.24 (SWCLK)
/RP2350A MCU/SWDIO_{MCU}: J3.2 (SWDIO), U4.25 (SWDIO)
/RP2350A MCU/UART1_{MCU}_RX: D18.2 (A), J4.10, U4.13 (GPIO9)
/RP2350A MCU/UART1_{MCU}_TX: D17.2 (A), J4.9, U4.12 (GPIO8)
/RP2350A MCU/USB_{MCU}_N: J2.A7 (D-), J2.B7 (D-), U4.51 (USB_DM)
/RP2350A MCU/USB_{MCU}_P: J2.A6 (D+), J2.B6 (D+), U4.52 (USB_DP)
unnamed: C113.1, D4.2 (A), J2.A4 (VBUS), J2.A9 (VBUS), J2.B4 (VBUS), J2.B9 (VBUS), R39.1, U2.2 (EN), U2.4 (IN)
unnamed: D9.1 (K), D11.1 (K), D13.1 (K), D14.1 (K)
unnamed: J2.A5 (CC1), R37.1
unnamed: J2.B5 (CC2), R38.1
unnamed: J2.SH (SHIELD), R36.1
unnamed: R42.2, SW3.2
unnamed: R44.1, SW4.2
unnamed: C114.1, R39.2, U2.5 (VCC)
unnamed: R42.1, R43.1, U3.1 (~CS)
unnamed: C121.1, R46.2, U4.46 (VREG_AVDD)
unnamed: L1.2, U4.48 (VREG_LX)
VCC_1V1_S0: C120.1, C122.1, C123.1, L1.1, U4.6 (DVDD), U4.23 (DVDD), U4.39 (DVDD), U4.50 (VREG_FB)
VCC_{GPIO}_3V3_S0: D11.2 (A); also elsewhere on the board
VCC_{GPIO}_5V0_S0: D9.2 (A); also elsewhere on the board
Vbus_USB_{MCU}: C116.1, R40.1, U2.3 (OUT)

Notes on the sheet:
W25Q128JVS
The default OVP is 6.1V
RP2350A MCU

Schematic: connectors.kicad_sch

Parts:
C390: 22u; C_0603_1608Metric; Mouser Part CL10A226MP8NUNE; LCSC Part C86295
C391, C392, C393: 1u; C_0201_0603Metric_Pad0.64x0.40mm_HandSolder; Mouser Part CL03A105KP3NSNC; LCSC Part C5209398
J16, J17: 1-2199230-5; PCIE-SMD_75P-P0.50_1-2199230-5; MPN 1-2199230-5; LCSC Part C590854
R193, R194, R195, R196: 22R; R_0402_1005Metric; Mouser Part 603-RC0402FR-0722RL; LCSC Part C114765
R197, R198: 10k; R_0402_1005Metric; Mouser Part 603-RC0402FR-0710KL; LCSC Part C60490
R199: 10k; R_0402_1005Metric; Mouser Part 603-RC0402FR-0710KL; LCSC Part C60490; not fitted

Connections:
/MIPI/CSI1_RX_CLK_N: J16.17
/MIPI/CSI1_RX_D0_N: J16.14
/MIPI/CSI1_RX_D1_P: J16.12
/MIPI/DSI0.TX_D2_P: J17.12; also elsewhere on the board
/MIPI/LCD_BL_PWM1_CH1_M0: J17.17; also elsewhere on the board
/MIPI/LCD_PWREN_H: J17.19; also elsewhere on the board
unnamed 552: J16.22; also elsewhere on the board
unnamed 553: J16.25; also elsewhere on the board

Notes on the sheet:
PCIE0_PWR_EN : Pull-UP to make it ON by Default OR Pull-Down to make it OFF by default
PCIe Connector

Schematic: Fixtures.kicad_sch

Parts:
FID1, FID2, FID3, FID4: Fiducial; Fiducial_0.5mm_Mask1.5mm
H1, H2, H3, H4: MountingHole_Pad; MountingHole_3.2mm_M3_Pad_Via
R208, R209, R210, R211: 0R; R_0402_1005Metric; Mouser Part 603-RC0402FR-070RL; LCSC Part C106231
TP1, TP2, TP3, TP4, TP5, TP6, TP7: TestPoint_Probe; TestPoint-0.5mm

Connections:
unnamed: H1.1 (1_1), R208.1
unnamed: H2.1 (1_1), R209.1
unnamed: H3.1 (1_1), R210.1
unnamed: H4.1 (1_1), R211.1
VDD2_DDR_S3: TP5.1 (1_1); also elsewhere on the board

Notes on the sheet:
Mechanical

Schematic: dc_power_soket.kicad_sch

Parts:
J1: Barrel_Jack_Switch; BarrelJack_CUI_PJ-063AH_Horizontal

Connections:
/RK3576 SOC/JTAG_TCK_M1 & UART0_TX_M0: J1.2; also elsewhere on the board
/RK3576 SOC/JTAG_TMS_M1 & UART0_RX_M0: J1.3; also elsewhere on the board
VCC_3.3v_S0: J1.1; also elsewhere on the board

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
